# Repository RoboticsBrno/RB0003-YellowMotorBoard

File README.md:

# RB0003-YellowMotorBoard
Motor board with encoder sensors for yellow motor.

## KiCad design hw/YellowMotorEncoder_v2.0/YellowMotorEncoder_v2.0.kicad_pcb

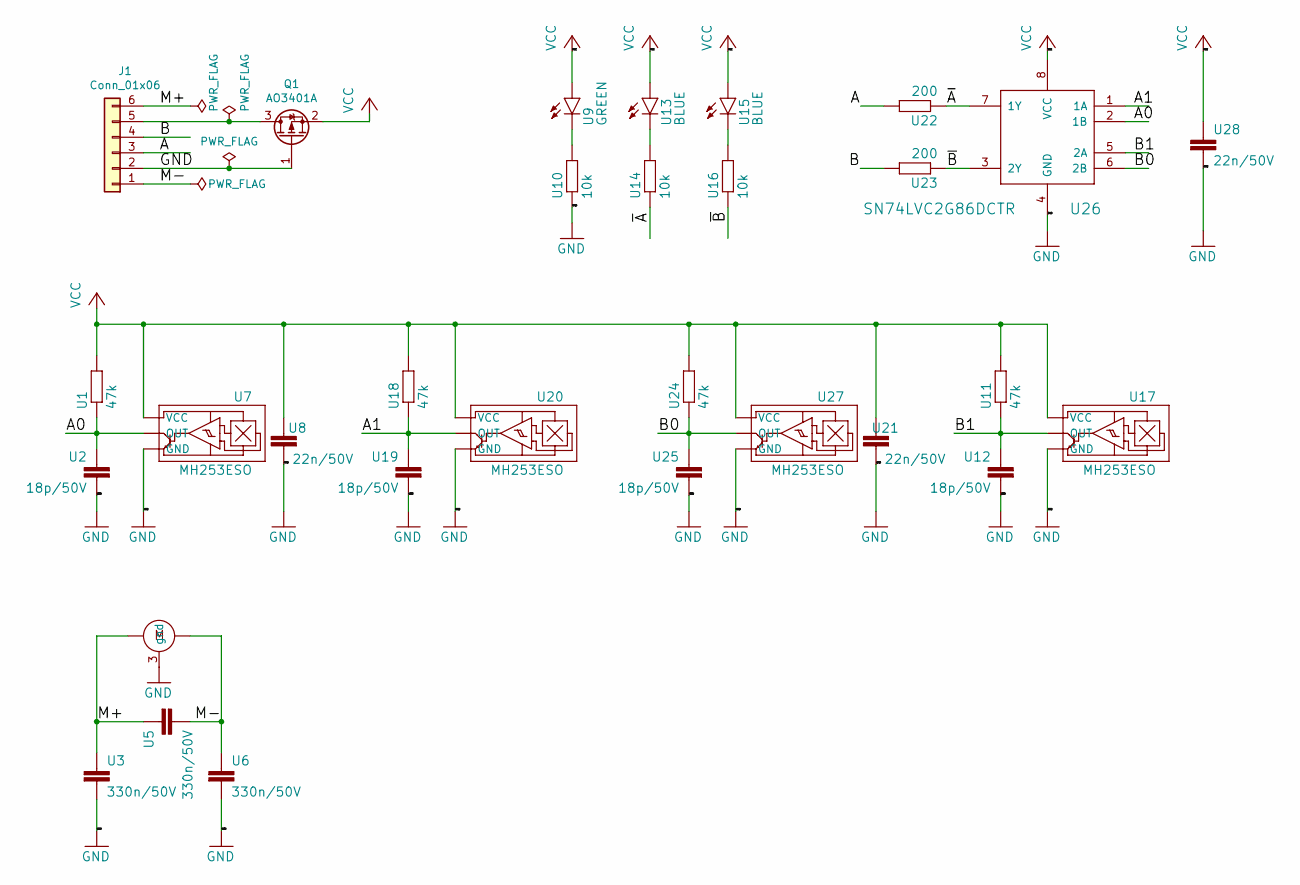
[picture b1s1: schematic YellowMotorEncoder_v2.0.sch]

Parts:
J1: Conn_01x06; PinHeader_1x06_P2.00mm_Vertical
Q1: AO3401A; SOT-23
U1, U11, U18, U24: 47k; R_0402_1005Metric; LCSC C25792
U2, U12, U19, U25: 18p/50V; C_0402_1005Metric; LCSC C1549
U3, U5, U6: 330n/50V; C_0805_2012Metric; LCSC C1740
U4: YELLOW_MOTORV2; MDCM
U7: MH253ESO; SOT-23; LCSC C114369
U8, U21, U28: 22n/50V; C_0402_1005Metric; LCSC C1532
U9: GREEN; LED_0603_1608Metric; LCSC C72043
U10, U14, U16: 10k; R_0402_1005Metric; LCSC C25744
U13, U15: BLUE; LED_0603_1608Metric; LCSC C72041
U17, U20, U27: MH253ESO; SOT-23
U22, U23: 200; R_0402_1005Metric; LCSC C25087
U26: SN74LVC2G86DCTR; MSOP-8_3x3mm_P0.65mm; LCSC C130023

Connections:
/A: J1.3, U22.2
/A0: U1.1, U2.1, U7.2 (OUT), U26.2 (1B)
/A1: U18.1, U19.1, U20.2 (OUT), U26.1 (1A)
/B: J1.4, U23.2
/B0: U24.1, U25.1, U26.6 (2B), U27.2 (OUT)
/B1: U11.1, U12.1, U17.2 (OUT), U26.5 (2A)
/M+: J1.6, U3.1, U4.2, U5.2
/M-: J1.1, U4.1, U5.1, U6.1
/~A: U14.1, U22.1, U26.7 (1Y)
/~B: U16.1, U23.1, U26.3 (2Y)
GND: J1.2, Q1.1 (G), U2.2, U3.2, U4.3 (gnd), U6.2, U7.3 (GND), U8.2, U10.1, U12.2, U17.3 (GND), U19.2, U20.3 (GND), U21.2, U25.2, U26.4 (GND), U27.3 (GND), U28.2
unnamed: J1.5, Q1.3 (D)
unnamed: U9.1 (C), U10.2
unnamed: U13.1 (C), U14.2
unnamed: U15.1 (C), U16.2
VCC: Q1.2 (S), U1.2, U7.1 (VCC), U8.1, U9.2 (A), U11.2, U13.2 (A), U15.2 (A), U17.1 (VCC), U18.2, U20.1 (VCC), U21.1, U24.2, U26.8 (VCC), U27.1 (VCC), U28.1

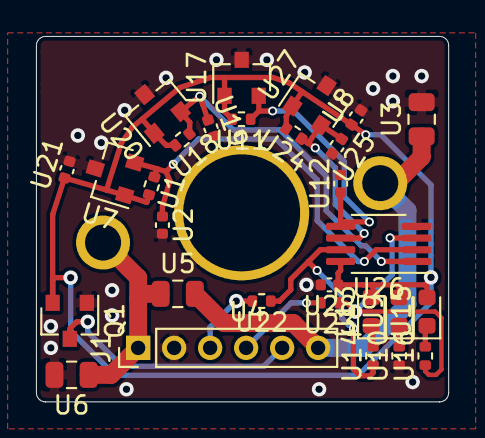
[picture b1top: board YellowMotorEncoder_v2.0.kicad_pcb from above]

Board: 2 copper layers, 22.9 x 20.3 mm, 30 parts (0 on the bottom side), 16 nets.

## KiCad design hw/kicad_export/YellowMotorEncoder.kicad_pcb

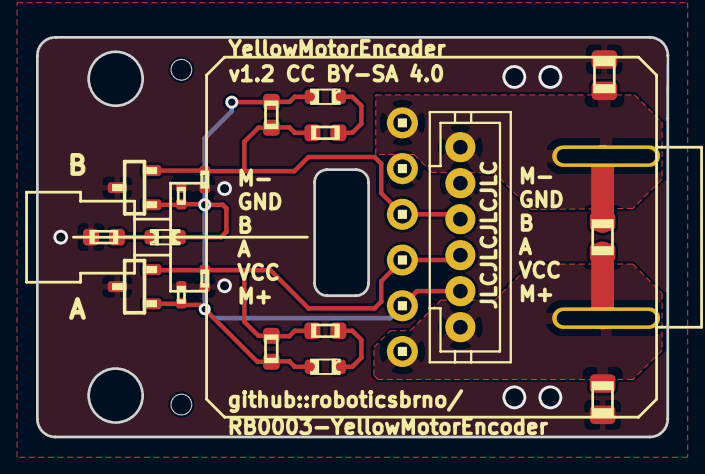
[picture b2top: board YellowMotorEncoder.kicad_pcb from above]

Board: 2 copper layers, 35.0 x 22.2 mm, 22 parts (0 on the bottom side), 9 nets.

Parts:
@HOLE0, @HOLE1: (no value)
C1, C2: 10n/50V; C0402
C3, C4, C5: 330n/50V; C0805
C6, C7: 18p/50V; C0402
JP1: 1X06
LED_A: RED; CHIPLED_0603
LED_B: RED; CHIPLED_0603
LED_POWER: RED; CHIPLED_0603
P1: M1; JST-PH6
R1, R2, R3: 1k; R0603
R4, R5: 47k; R0603
U$1, U$2: MH253ESO; SOT23
U$3: YELLOW_MOTOR

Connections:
A: C6.1, JP1.4, P1.3, R2.1, R4.1, U$1.2
B: C7.1, JP1.3, P1.4, R3.1, R5.1, U$2.2
GND: C1.2, C2.2, C3.2, C4.2, C6.2, C7.2, JP1.2, P1.5, R1.1, U$1.3, U$2.3
LED_POWER: LED_POWER.C, R1.2
LED_SIDE1: LED_A.C, R2.2
LED_TOP1: LED_B.C, R3.2
M+: C3.1, C5.1, JP1.6, P1.1, U$3.P$2
M-: C4.1, C5.2, JP1.1, P1.6, U$3.P$1
VCC: C1.1, C2.1, JP1.5, LED_A.A, LED_B.A, LED_POWER.A, P1.2, R4.2, R5.2, U$1.1, U$2.1

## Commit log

2020-05-08 Add YellowMotorBoard board
    - need to finish routing
2020-05-08 Finish routing of the board
2020-05-09 Finish routing YellowMotorEncoder v1.0
    - route PCB
    - correct position of mounting holes
    - fix connectors signal
2020-05-11 Swap encoder power polarity
2020-05-11 Fixed LEDs orientation
2020-05-11 Rerouted board
2020-05-11 Improve layout for manufacturing
    - add JLC order number to silkscreen
    - add JLC tooling holes
    - fix rotation of hall sensors (`hall_sensor.lbr`)
    - decrease size of silkscreen text- board name, version, licence and URL
2020-05-24 Add and move motor polygons
    - add bottom polygons for motor pins/soldering holes
    - move unmask polygons for motor pads to not overlap with M+/M-
2020-05-24 Change license from `CC0-1.0` to `CC BY-SA 4.0`
2020-05-24 Update/add licenses and authors in libraries
    - not update the libraries inside `.brd` and `.sch` project files
2020-05-24 Create folder `YellowMotorBoard_v1.0` with manufactured Eagle PCB files
2020-05-24 Create version 1.1 - change shape of the motor holes/pads
    - create folder `YellowMotorBoard_v1.1` with manufactured Eagle PCB files
    - shape of motor holes (slotted holes) create according these tutorials
    - https://www.autodesk.com/products/eagle/blog/what-you-didnt-know-about-eagle-slotted-holes/
    - http://blog.snapeda.com/2019/05/30/how-snapeda-creates-slotted-holes-on-eagle/
    - `YellowMotorEncoder_JLCPCB.cam`
    - add Milling (46) layer
2020-06-14 Make many improvements according testing v1.0 and v1.1 boards
    - increase version number from v1.1 to v1.2
    - decrease width of board from 22.4 to 22.2 mm
    - move all parts to corresponding position with respect to the board center
    - move hall sensor:
    - Y axis: 0.25 mm closer to the center of board (distance between both sensors is -0.5 mm)
    - X axis: 0.8 mm in motor direction
2020-06-15 Add Kicad export and KiKit panelizer makefile
    - fix position of text labels "A", "B"
    - export project to Kicad and panelize with KiKit
    - add configuration for TravisCI web page build
2020-06-15 Fix radius in Makefile for KiKit panelization
    - `radius` must be smaller then `space` / 2, NOT smaller or equal
2020-06-22 Improve Makefile and add F.Mask polygon to kicad_export board
2020-06-24 Update shape of motor's slotted holes in Kicad exported board
    - change the shape from circle to oval as this feature is supported in Kicad
    - fix missing capacitor in KiKit export - move their label inside PCB border
2020-06-26 Release/manufacture version 1.2
    Summary:
    - decrease width of the board from 22.4 to 22.2 mm
    - move hall sensor:
    - Y axis: 0.25 mm closer to the centre of the board (distance between both sensors is -0.5 mm)
    - X axis: 0.8 mm in motor direction
    - move slotted holes for motor contact soldering approx. 0.5 mm far from hall sensors for better assembly
2020-07-01 Deploy RoboticsBrno/RB0003-YellowMotorEncoder to github.com/RoboticsBrno/RB0003-YellowMotorEncoder.git:gh-pages
2020-09-20 FourProbes
2020-09-20 librarys
2020-09-20 ochrany
2020-10-14 YellowMotorEncoder_V2.0
    New design with four sensors and xor to combine two signals to one.
    Design is in KiCad.
2020-10-14 3D_viewer
    i add 3d model of motor and connector
2020-10-15 .pro
    i add missing soubor
2020-10-16 rotate sensors
    I changing position of sensors and rotating it in circle around hole for shaft of motor.

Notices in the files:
hw/kicad_export/YellowMotorEncoder.kicad_pcb:
v1.2 CC BY-SA 4.0
